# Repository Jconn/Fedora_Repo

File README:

README file for the MAAV EAGLE git repo

*Do not add gerber files or zip files to the repo

*Edit the .gitignore file with any extensions that for gerber files if encountered

*Don't forget to add your name and email address your local config

*If you find errors in libraries, please fix them imediately or contact the author to report the error.

*You should not trust any of the files in this repo.  PLEASE VERIFY ALL COMPONENTS FOR YOURSELF!

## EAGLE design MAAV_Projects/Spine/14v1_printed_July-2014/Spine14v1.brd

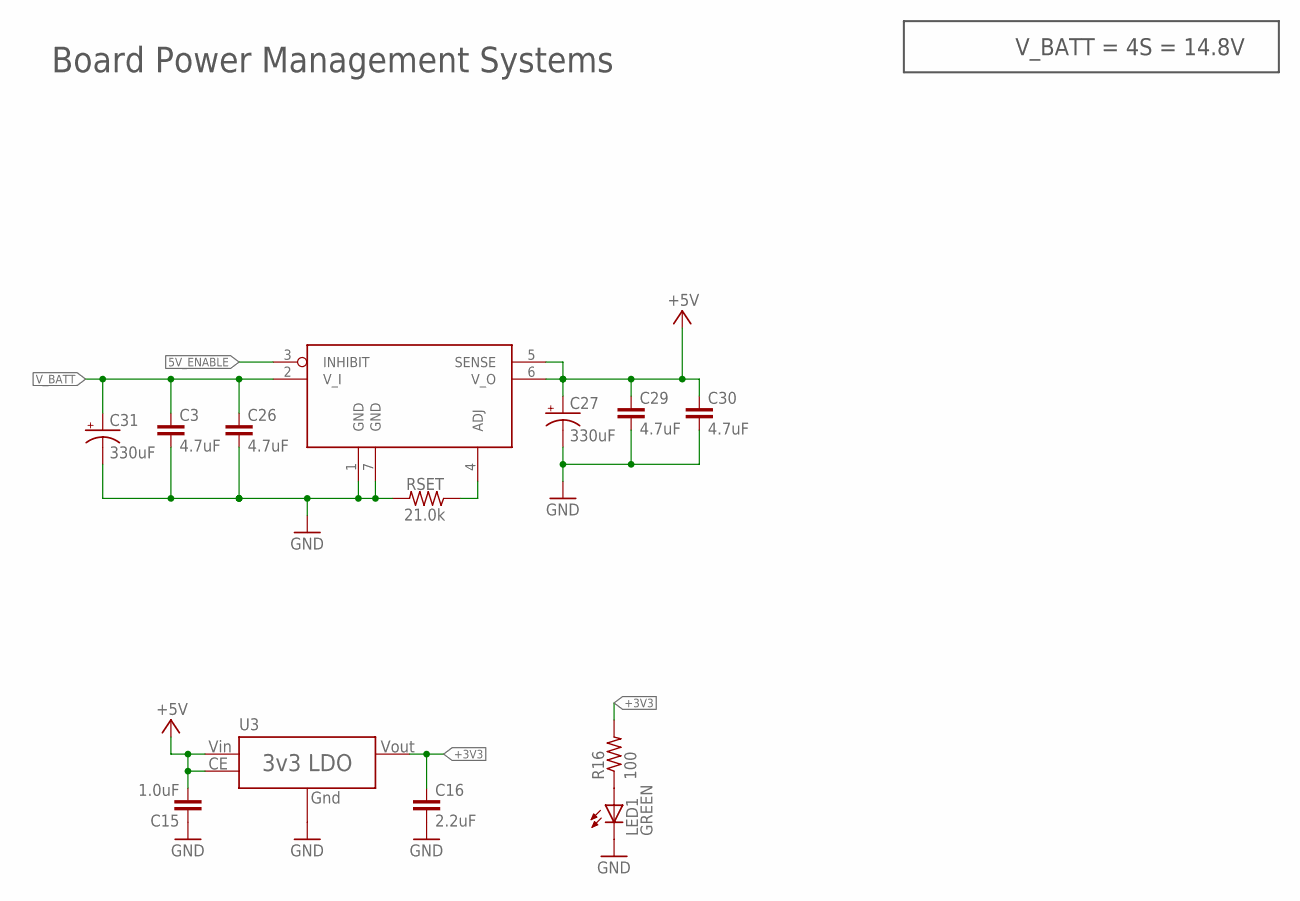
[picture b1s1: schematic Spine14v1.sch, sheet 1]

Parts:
C3, C26, C29, C30: 4.7uF; C1206; DIGIKEY# 587-2994-1-ND
C15: 1.0uF; C0805
C16: 2.2uF; C0805
C27, C31: 330uF; PANASONIC_F; DIGIKEY PCE3779CT-ND
LED1: GREEN; CHIPLED_0603
R16: 100; R0603
RSET: 21.0k; R0603
U3: XC6210; SOT-25
U$5: POWER-MODULE-TI-6A_SOLDERLESS_TERMINAL; POWER-MOD-TI-6A-SOLDERLESS-TERMINAL

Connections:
5V_ENABLE: U$5.3 (INHIBIT); also elsewhere on the board
+3V3: C16.1, R16.2, U3.5 (VOUT); also elsewhere on the board
+5V: C15.2, C27.+, C29.1, C30.1, U3.1 (VIN), U3.3 (CE), U$5.5 (SENSE), U$5.6 (V_O); also elsewhere on the board
GND: C3.2, C15.1, C16.2, C26.2, C27.-, C29.2, C30.2, C31.-, LED1.C, RSET.2, U3.2 (GND), U$5.1 (GND), U$5.7 (GND); also elsewhere on the board
unnamed: LED1.A, R16.1
unnamed: RSET.1, U$5.4 (ADJ)
V_BATT: C3.1, C26.1, C31.+, U$5.2 (V_I); also elsewhere on the board

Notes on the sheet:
Board Power Management Systems
V_BATT = 4S = 14.8V

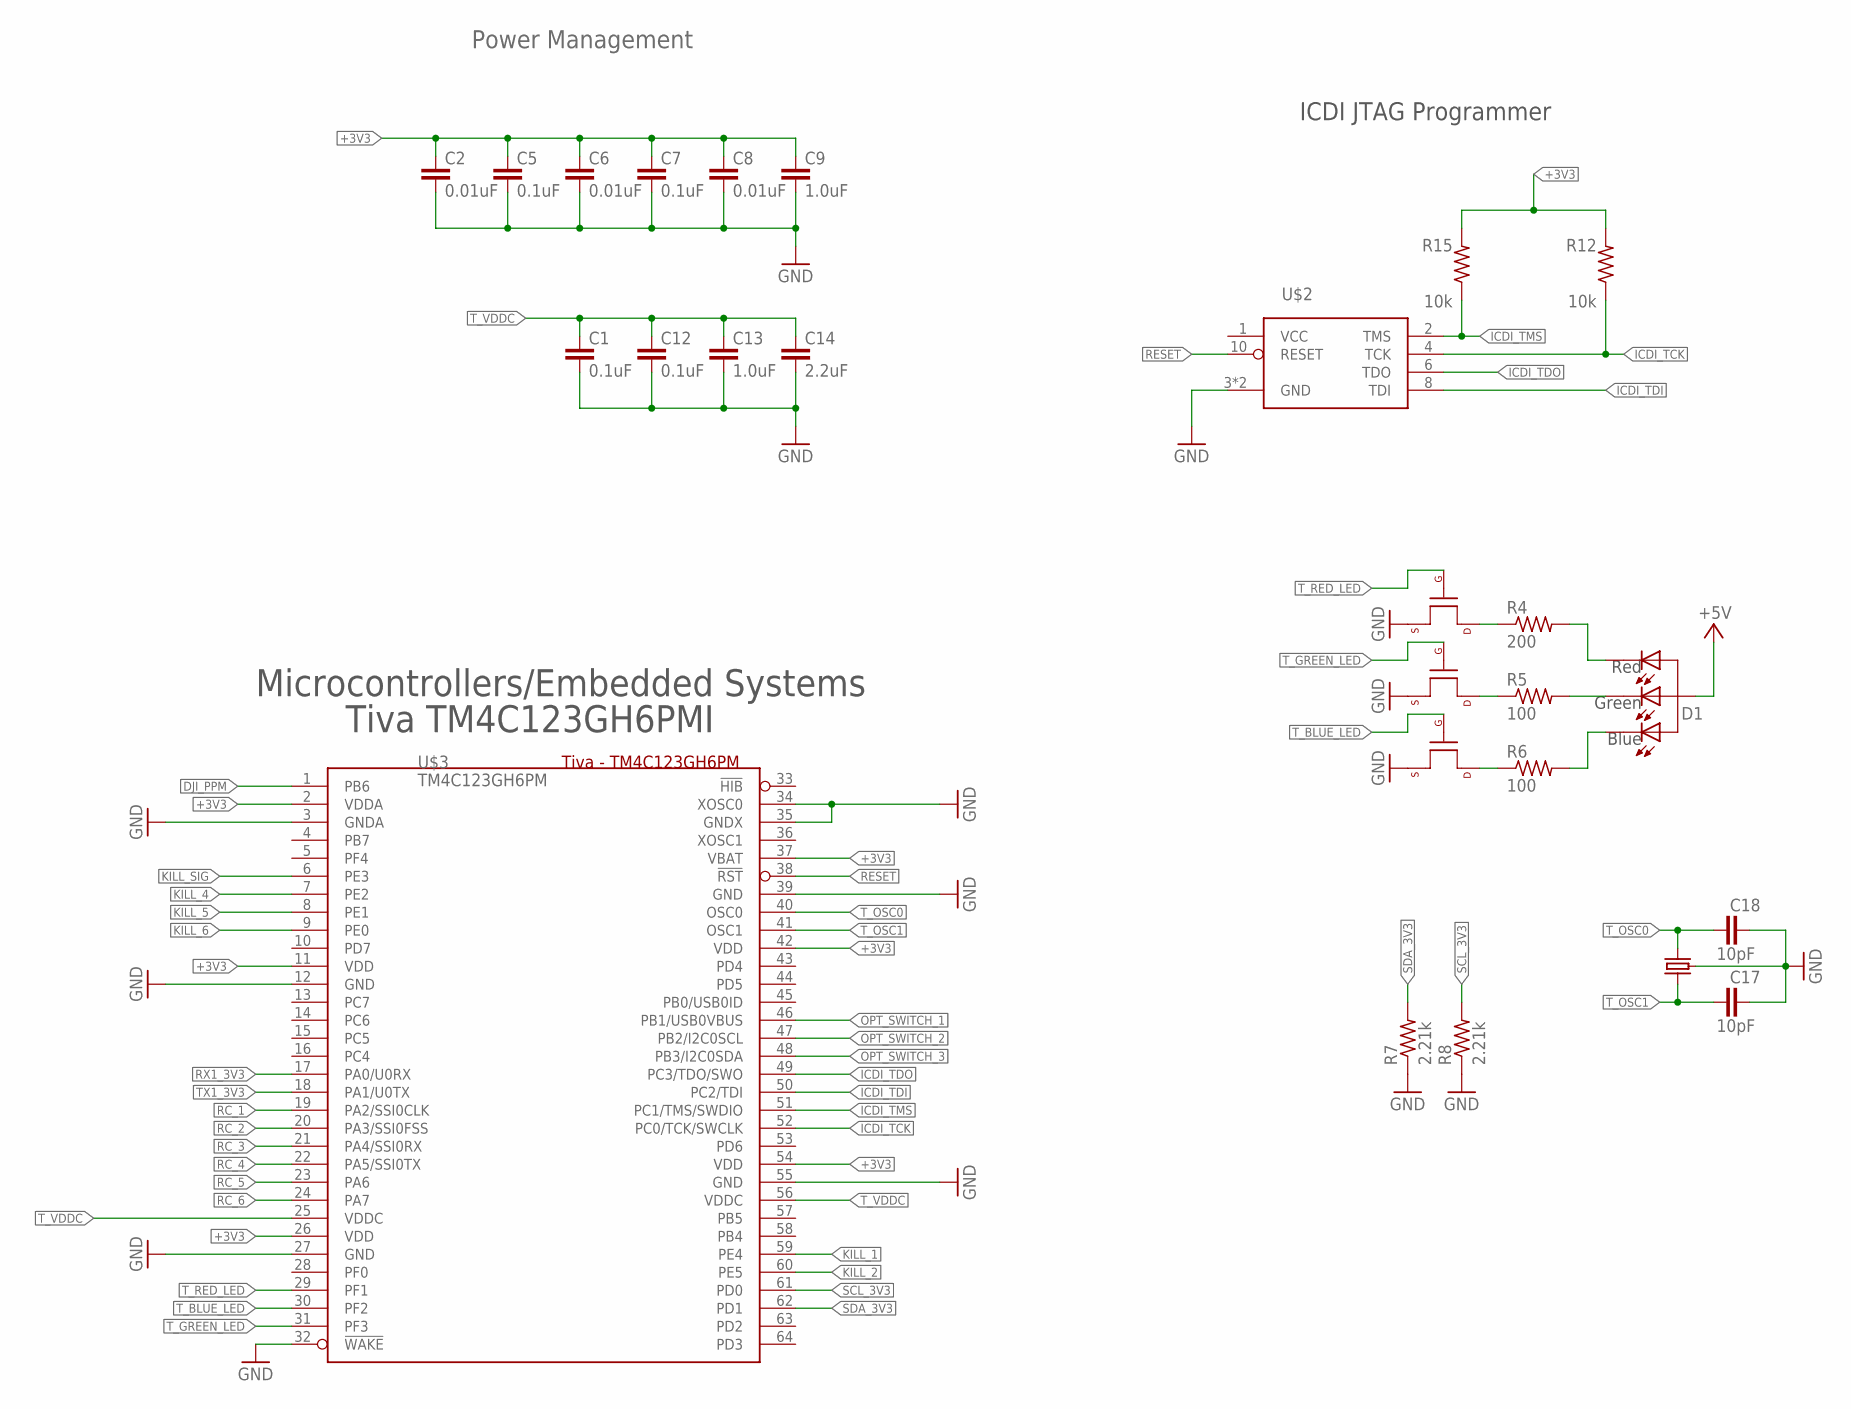
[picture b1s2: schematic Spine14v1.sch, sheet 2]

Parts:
C1, C5, C7, C12: 0.1uF; C0603
C2, C6, C8: 0.01uF; C0603
C9: 1.0uF; C0603
C13: 1.0uF; C0805
C14: 2.2uF; C0805
C17, C18: 10pF; C0603; DIGIKEY# 399-1049-1-ND
D1: LED_RGB_CA; LED_RGB_0606
Q2, Q3, Q4: MOSFET-NCHANNELSMD; SOT23-3; DIGIKEY# BSN20-7DICT-ND
R4: 200; R0603
R5, R6: 100; R0603
R7, R8: 2.21k; R0603
R12, R15: 10k; R0603
U$1: CRYSTAL_403C11E16; 4-SMD-SWITCH
U$2: JTAG-ARM_TC-10; TC2050-IDC
U$3: TM4C123GH6PM; DIGIKEY# 296-35849-ND

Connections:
+3V3: C2.1, C5.1, C6.1, C7.1, C8.1, C9.1, R12.2, R15.2, U$3.2 (VDDA), U$3.11 (VDD), U$3.26 (VDD), U$3.37 (VBAT), U$3.42 (VDD), U$3.54 (VDD); also elsewhere on the board
+5V: D1.1 (A); also elsewhere on the board
DJI_PPM: U$3.1 (PB6); also elsewhere on the board
GND: C1.2, C2.2, C5.2, C6.2, C7.2, C8.2, C9.2, C12.2, C13.2, C14.2, C17.2, C18.2, Q2.2 (S), Q3.2 (S), Q4.2 (S), R7.1, R8.1, U$1.2 (GND), U$1.4 (GND), U$2.3 (GND), U$2.9 (GND), U$3.3 (GNDA), U$3.12 (GND), U$3.27 (GND), U$3.32 (!WAKE), U$3.34 (XOSC0), U$3.35 (GNDX), U$3.39 (GND), U$3.55 (GND); also elsewhere on the board
ICDI_TCK: R12.1, U$2.4 (TCK), U$3.52 (PC0/TCK/SWCLK)
ICDI_TDI: U$2.8 (TDI), U$3.50 (PC2/TDI)
ICDI_TDO: U$2.6 (TDO), U$3.49 (PC3/TDO/SWO)
ICDI_TMS: R15.1, U$2.2 (TMS), U$3.51 (PC1/TMS/SWDIO)
KILL_1: U$3.59 (PE4); also elsewhere on the board
KILL_2: U$3.60 (PE5); also elsewhere on the board
KILL_4: U$3.7 (PE2); also elsewhere on the board
KILL_5: U$3.8 (PE1); also elsewhere on the board
KILL_6: U$3.9 (PE0); also elsewhere on the board
KILL_SIG: U$3.6 (PE3); also elsewhere on the board
unnamed: Q4.3 (D), R4.1
unnamed: Q3.3 (D), R5.1
unnamed: Q2.3 (D), R6.1
unnamed: D1.2 (R), R4.2
unnamed: D1.3 (G), R5.2
unnamed: D1.4 (B), R6.2
OPT_SWITCH_1: U$3.46 (PB1/USB0VBUS); also elsewhere on the board
OPT_SWITCH_2: U$3.47 (PB2/I2C0SCL); also elsewhere on the board
OPT_SWITCH_3: U$3.48 (PB3/I2C0SDA); also elsewhere on the board
RC_1: U$3.19 (PA2/SSI0CLK); also elsewhere on the board
RC_2: U$3.20 (PA3/SSI0FSS); also elsewhere on the board
RC_3: U$3.21 (PA4/SSI0RX); also elsewhere on the board
RC_4: U$3.22 (PA5/SSI0TX); also elsewhere on the board
RC_5: U$3.23 (PA6); also elsewhere on the board
RC_6: U$3.24 (PA7); also elsewhere on the board
RESET: U$2.10 (RESET), U$3.38 (!RST); also elsewhere on the board
RX1_3V3: U$3.17 (PA0/U0RX); also elsewhere on the board
SCL_3V3: R8.2, U$3.61 (PD0); also elsewhere on the board
SDA_3V3: R7.2, U$3.62 (PD1); also elsewhere on the board
TX1_3V3: U$3.18 (PA1/U0TX); also elsewhere on the board
T_BLUE_LED: Q2.1 (G), U$3.30 (PF2)
T_GREEN_LED: Q3.1 (G), U$3.31 (PF3)
T_OSC0: C18.1, U$1.3 (2), U$3.40 (OSC0)
T_OSC1: C17.1, U$1.1, U$3.41 (OSC1)
T_RED_LED: Q4.1 (G), U$3.29 (PF1)
T_VDDC: C1.1, C12.1, C13.1, C14.1, U$3.25 (VDDC), U$3.56 (VDDC)

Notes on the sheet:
Microcontrollers/Embedded Systems
Power Management
Tiva TM4C123GH6PMI
ICDI JTAG Programmer

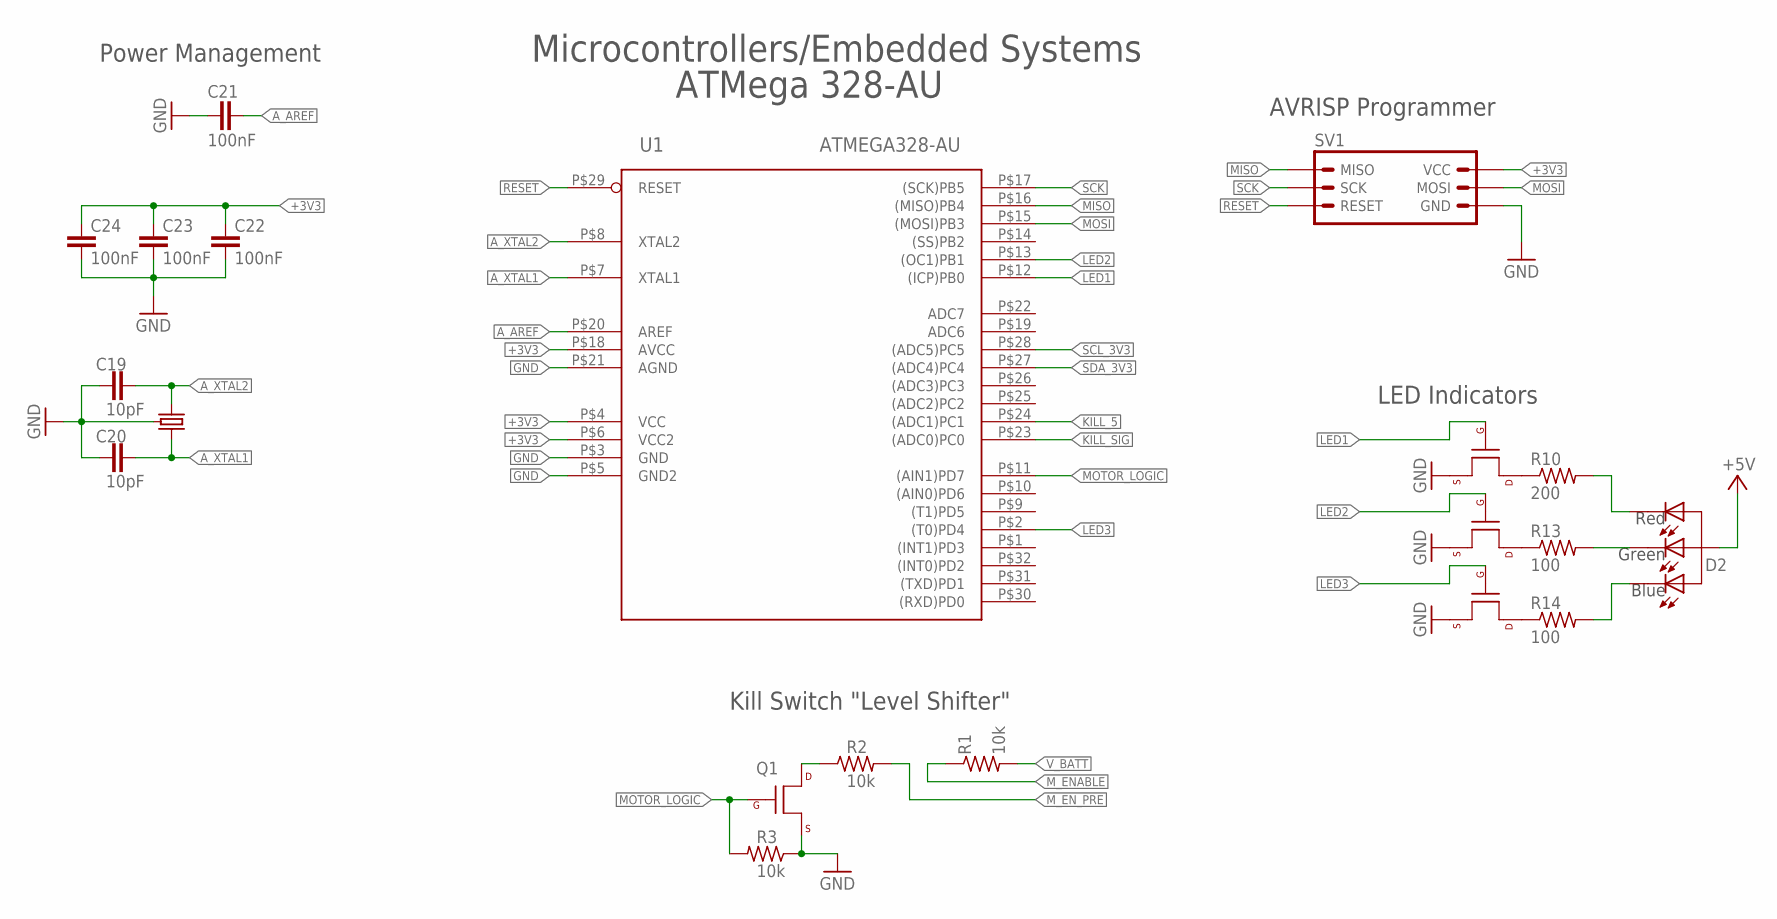
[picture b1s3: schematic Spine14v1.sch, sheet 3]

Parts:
C19, C20: 10pF; C0603; DIGIKEY# 399-1049-1-ND
C21, C22, C23, C24: 100nF; C0603; DIGIKEY# 1276-1000-1-ND
D2: LED_RGB_CA; LED_RGB_0606
Q1, Q6, Q7, Q8: MOSFET-NCHANNELSMD; SOT23-3; DIGIKEY# BSN20-7DICT-ND
R1, R2, R3: 10k; R0603
R10: 200; R0603
R13, R14: 100; R0603
SV1: AVRISP-6_3X2_PLUG_OF_NAILS; TC2030-IDC
U1: ATMEGA328-AU; 32-TQFP; DIGIKEY# ATMEGA328-AU-ND
U$6: CRYSTAL_403C11E16; 4-SMD-SWITCH

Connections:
+3V3: C22.1, C23.1, C24.1, SV1.6 (VCC), U1.P$4 (VCC), U1.P$6 (VCC2), U1.P$18 (AVCC); also elsewhere on the board
+5V: D2.1 (A); also elsewhere on the board
A_AREF: C21.1, U1.P$20 (AREF)
A_XTAL1: C20.2, U1.P$7 (XTAL1), U$6.3 (2)
A_XTAL2: C19.2, U1.P$8 (XTAL2), U$6.1
GND: C19.1, C20.1, C21.2, C22.2, C23.2, C24.2, Q1.2 (S), Q6.2 (S), Q7.2 (S), Q8.2 (S), R3.1, SV1.4 (GND), U1.P$3 (GND), U1.P$5 (GND2), U1.P$21 (AGND), U$6.2 (GND), U$6.4 (GND); also elsewhere on the board
KILL_5: U1.P$24 ((ADC1)PC1); also elsewhere on the board
KILL_SIG: U1.P$23 ((ADC0)PC0); also elsewhere on the board
LED1: Q8.1 (G), U1.P$12 ((ICP)PB0)
LED2: Q7.1 (G), U1.P$13 ((OC1)PB1)
LED3: Q6.1 (G), U1.P$2 ((T0)PD4)
MISO: SV1.1 (MISO), U1.P$16 ((MISO)PB4)
MOSI: SV1.5 (MOSI), U1.P$15 ((MOSI)PB3)
MOTOR_LOGIC: Q1.1 (G), R3.2, U1.P$11 ((AIN1)PD7)
M_ENABLE: R1.1; also elsewhere on the board
M_EN_PRE: R2.2; also elsewhere on the board
unnamed: Q1.3 (D), R2.1
unnamed: Q8.3 (D), R10.1
unnamed: Q7.3 (D), R13.1
unnamed: Q6.3 (D), R14.1
unnamed: D2.2 (R), R10.2
unnamed: D2.3 (G), R13.2
unnamed: D2.4 (B), R14.2
RESET: SV1.3 (RESET), U1.P$29 (RESET); also elsewhere on the board
SCK: SV1.2 (SCK), U1.P$17 ((SCK)PB5)
SCL_3V3: U1.P$28 ((ADC5)PC5); also elsewhere on the board
SDA_3V3: U1.P$27 ((ADC4)PC4); also elsewhere on the board
V_BATT: R1.2; also elsewhere on the board

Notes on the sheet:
Microcontrollers/Embedded Systems
ATMega 328-AU
AVRISP Programmer
Power Management
LED Indicators
Kill Switch "Level Shifter"

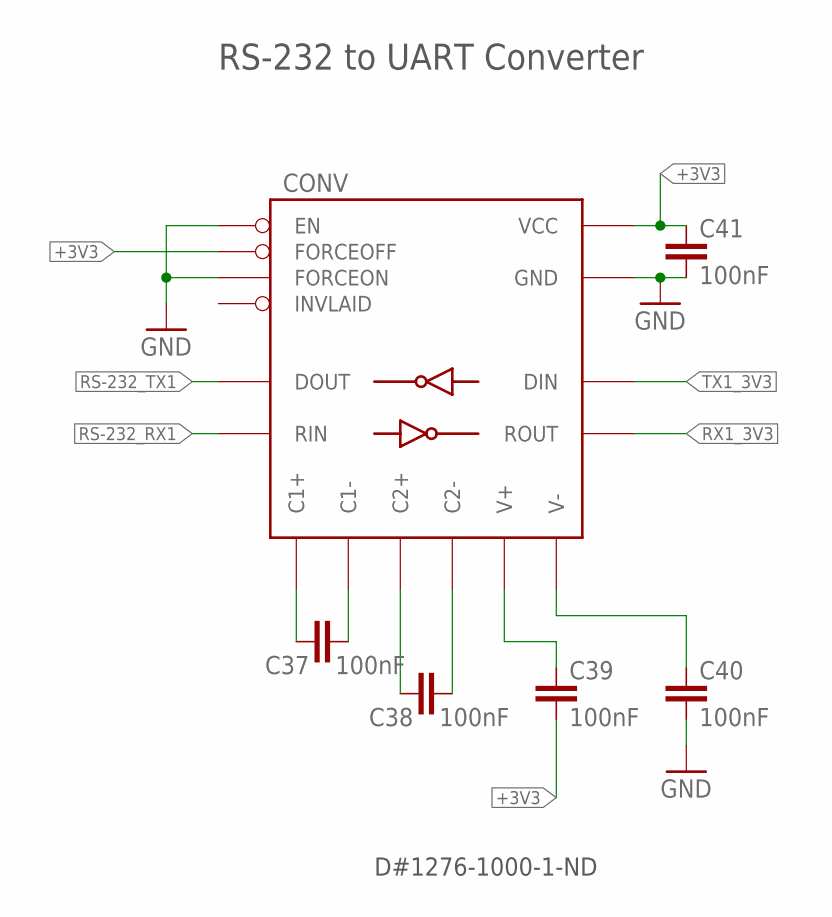
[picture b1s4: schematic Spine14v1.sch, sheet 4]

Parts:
C37, C41: 100nF; C0603; DIGIKEY# 1276-1000-1-ND
C38, C39, C40: 100nF; C0805
CONV: MAX3221-RS232; 16-TSSOP; DIGIKEY# 296-19825-1-ND

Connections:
+3V3: C39.2, C41.1, CONV.P$15 (VCC), CONV.P$16 (FORCEOFF); also elsewhere on the board
GND: C40.2, C41.2, CONV.P$1 (EN), CONV.P$12 (FORCEON), CONV.P$14 (GND); also elsewhere on the board
unnamed: C37.1, CONV.P$2 (C1+)
unnamed: C39.1, CONV.P$3 (V+)
unnamed: C40.1, CONV.P$7 (V-)
unnamed: C37.2, CONV.P$4 (C1-)
unnamed: C38.1, CONV.P$5 (C2+)
unnamed: C38.2, CONV.P$6 (C2-)
RS-232_RX1: CONV.P$8 (RIN); also elsewhere on the board
RS-232_TX1: CONV.P$13 (DOUT); also elsewhere on the board
RX1_3V3: CONV.P$9 (ROUT); also elsewhere on the board
TX1_3V3: CONV.P$11 (DIN); also elsewhere on the board

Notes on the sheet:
RS-232 to UART Converter
D#1276-1000-1-ND

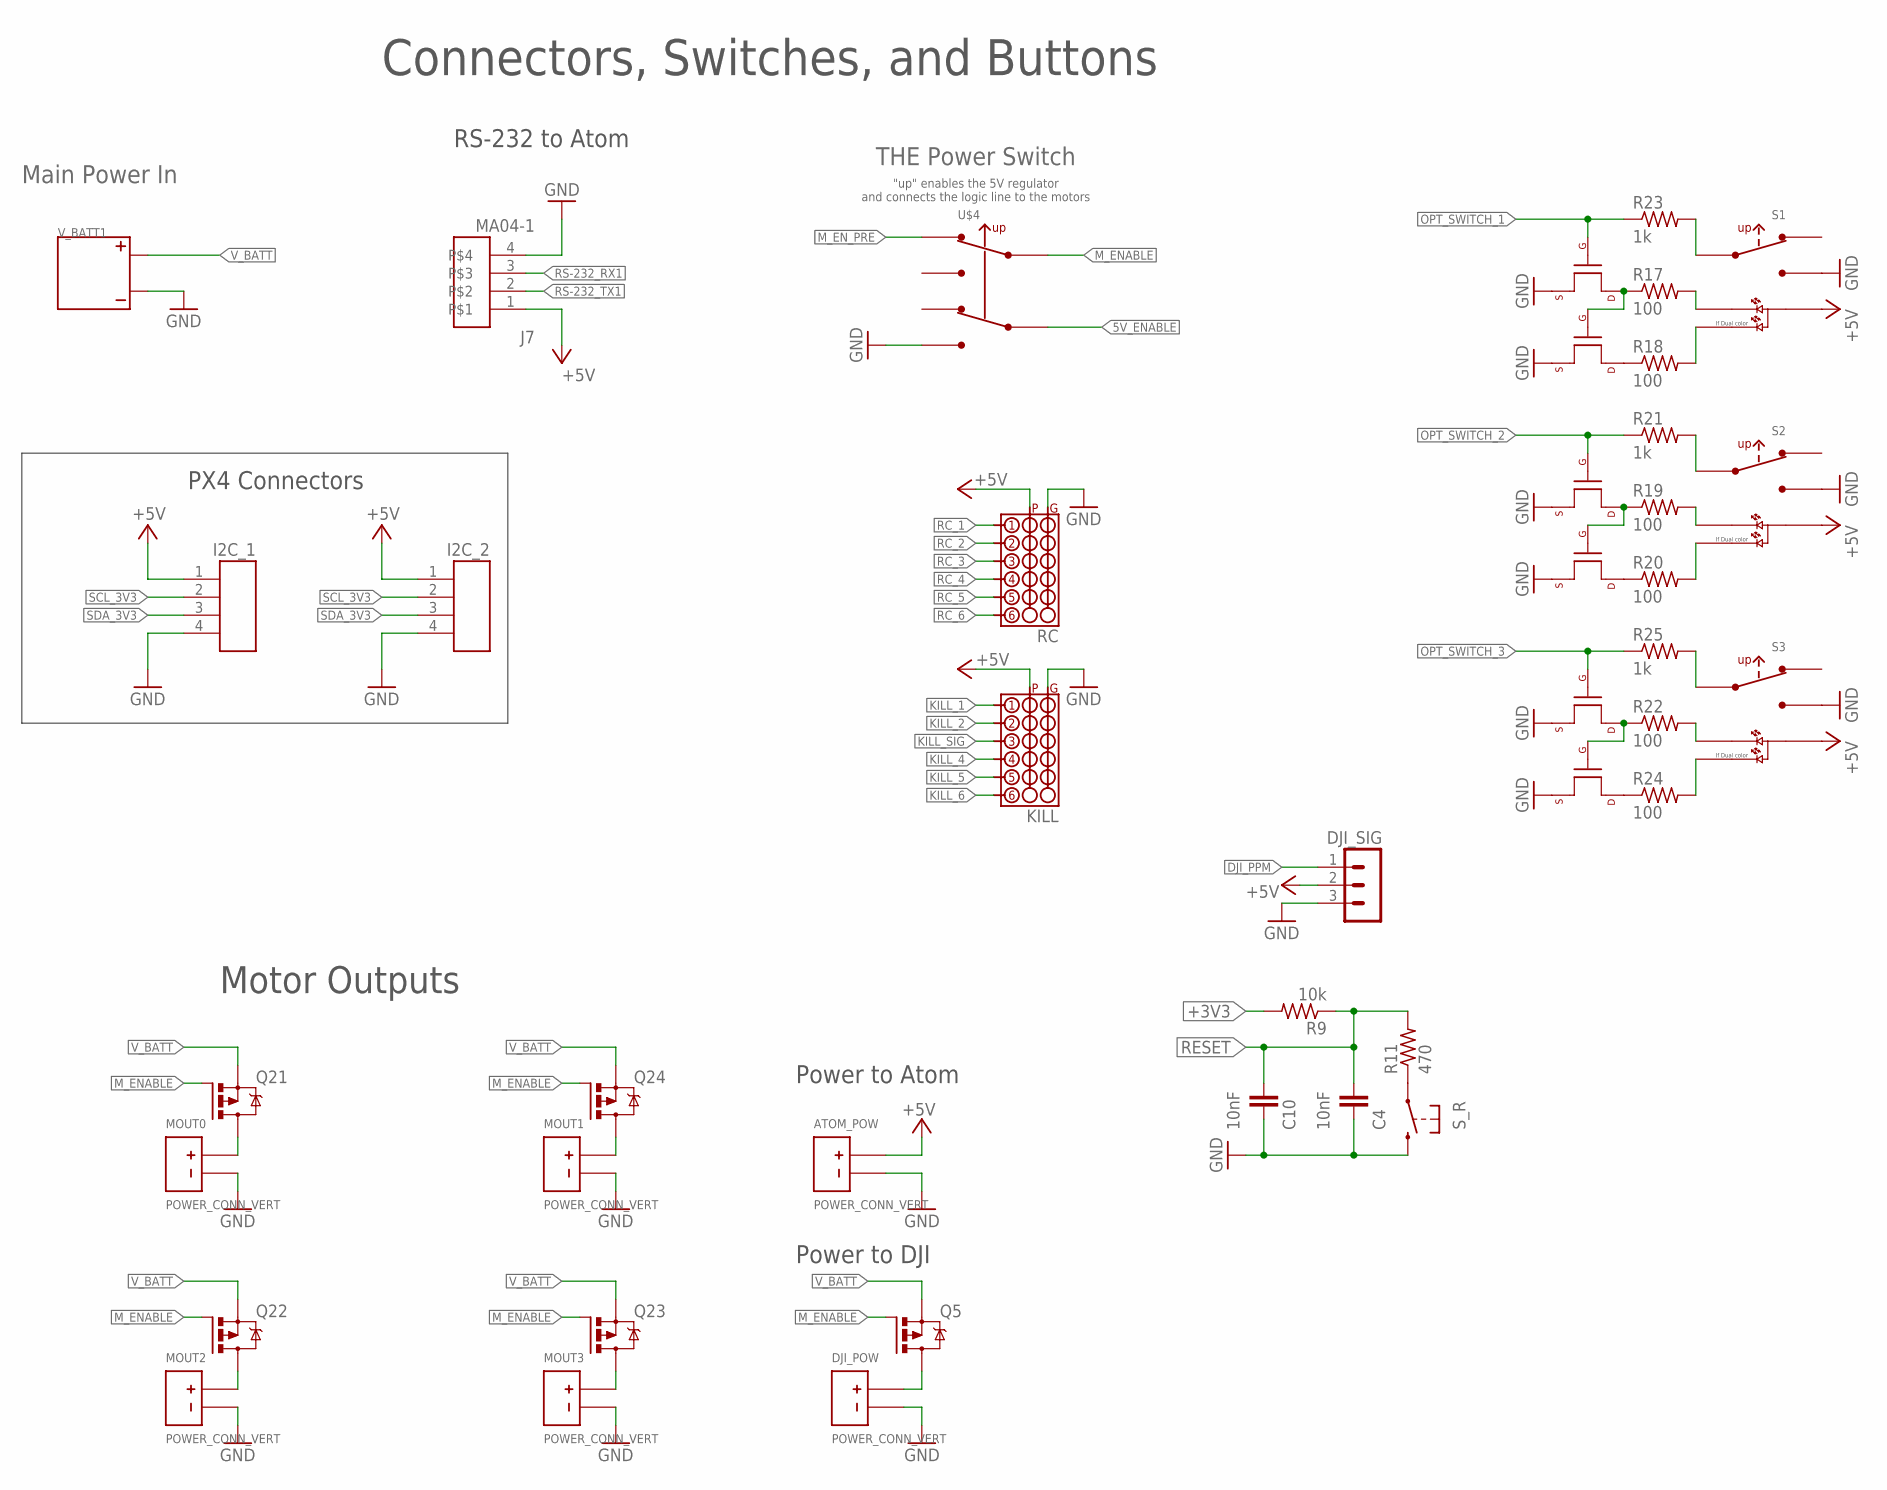
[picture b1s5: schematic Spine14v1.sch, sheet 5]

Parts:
ATOM_POW: POWER_CONN_VERT; POWER_CONN
C4, C10: 10nF; C0603
DJI_POW: POWER_CONN_VERT; POWER_CONN
DJI_SIG: MA03-1
I2C_1, I2C_2: CONN_HEADER_4POS_RIGHT_ANGLE_I2C; CONN_HEADER_4POS_1.25MM_SMD
J7: MA04-1; MA-04-SMD
KILL: RC_RECIEVER_RECEP
MOUT0, MOUT1, MOUT2, MOUT3: POWER_CONN_VERT; POWER_CONN
Q5, Q21, Q22, Q23, Q24: P-MOSFET-SO8POWER-PAK; SO-8_POWER-PAK
Q9, Q10, Q11, Q12, Q13, Q14: MOSFET-NCHANNELSMD; SOT23-3; DIGIKEY# BSN20-7DICT-ND
R9: 10k; R0603
R11: 470; R0603
R17, R18, R19, R20, R22, R24: 100; R0603
R21, R23, R25: 1k; R0603
RC: RC_RECIEVER_RECEP
S1, S2, S3: SWITCH_SPDT_ILUMINATED_2COLOR_VERT_ILLUMINATED; NKK_VERT_SWITCH_6PIN
S_R: TACT_BUTTONSMD; TACT-MOM-SMD
U$4: JON_LIB_SWITCH_DPDT; JON_LIB_SWITCH_VERT_DPDT
V_BATT1: BATT-CONN-50A_MINI-FIT-SR_THRU-HOLE; BATT-CONN-50A

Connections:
5V_ENABLE: U$4.P$5; also elsewhere on the board
+3V3: R9.2; also elsewhere on the board
+5V: ATOM_POW.P1, DJI_SIG.2, I2C_1.1, I2C_2.1, J7.1, KILL.VCC, KILL.VCC2 (VCC), RC.VCC, RC.VCC2 (VCC), S1.P$5, S2.P$5, S3.P$5; also elsewhere on the board
DJI_PPM: DJI_SIG.1; also elsewhere on the board
GND: ATOM_POW.P2 (N), C4.2, C10.2, DJI_POW.P2 (N), DJI_SIG.3, I2C_1.4, I2C_2.4, J7.4, KILL.GND, KILL.GND2 (GND), MOUT0.P2 (N), MOUT1.P2 (N), MOUT2.P2 (N), MOUT3.P2 (N), Q9.2 (S), Q10.2 (S), Q11.2 (S), Q12.2 (S), Q13.2 (S), Q14.2 (S), RC.GND, RC.GND2 (GND), S1.P$1, S2.P$1, S3.P$1, S_R.S, S_R.S1 (S), U$4.P$6, V_BATT1.GND-1 (GND), V_BATT1.GND-2 (GND); also elsewhere on the board
KILL_1: KILL.P$1; also elsewhere on the board
KILL_2: KILL.P$2; also elsewhere on the board
KILL_4: KILL.P$4; also elsewhere on the board
KILL_5: KILL.P$5; also elsewhere on the board
KILL_6: KILL.P$6; also elsewhere on the board
KILL_SIG: KILL.P$3; also elsewhere on the board
M_ENABLE: Q5.G, Q21.G, Q22.G, Q23.G, Q24.G, U$4.P$2; also elsewhere on the board
M_EN_PRE: U$4.P$1; also elsewhere on the board
unnamed: MOUT0.P1, Q21.D1, Q21.D2 (D1), Q21.D3 (D1), Q21.D4 (D1), Q21.D5 (D1)
unnamed: Q9.1 (G), Q10.3 (D), R17.1
unnamed: R11.1, S_R.P, S_R.P1
unnamed: MOUT1.P1, Q24.D1, Q24.D2 (D1), Q24.D3 (D1), Q24.D4 (D1), Q24.D5 (D1)
unnamed: MOUT2.P1, Q22.D1, Q22.D2 (D1), Q22.D3 (D1), Q22.D4 (D1), Q22.D5 (D1)
unnamed: MOUT3.P1, Q23.D1, Q23.D2 (D1), Q23.D3 (D1), Q23.D4 (D1), Q23.D5 (D1)
unnamed: DJI_POW.P1, Q5.D1, Q5.D2 (D1), Q5.D3 (D1), Q5.D4 (D1), Q5.D5 (D1)
unnamed: Q9.3 (D), R18.1
unnamed: Q11.1 (G), Q12.3 (D), R19.1
unnamed: Q11.3 (D), R20.1
unnamed: R19.2, S2.P$6
unnamed: R20.2, S2.P$4
unnamed: R23.2, S1.P$2
unnamed: R21.2, S2.P$2
unnamed: R17.2, S1.P$6
unnamed: R18.2, S1.P$4
unnamed: Q13.1 (G), Q14.3 (D), R22.1
unnamed: Q13.3 (D), R24.1
unnamed: R22.2, S3.P$6
unnamed: R24.2, S3.P$4
unnamed: R25.2, S3.P$2
OPT_SWITCH_1: Q10.1 (G), R23.1; also elsewhere on the board
OPT_SWITCH_2: Q12.1 (G), R21.1; also elsewhere on the board
OPT_SWITCH_3: Q14.1 (G), R25.1; also elsewhere on the board
RC_1: RC.P$1; also elsewhere on the board
RC_2: RC.P$2; also elsewhere on the board
RC_3: RC.P$3; also elsewhere on the board
RC_4: RC.P$4; also elsewhere on the board
RC_5: RC.P$5; also elsewhere on the board
RC_6: RC.P$6; also elsewhere on the board
RESET: C4.1, C10.1, R9.1, R11.2; also elsewhere on the board
RS-232_RX1: J7.3; also elsewhere on the board
RS-232_TX1: J7.2; also elsewhere on the board
SCL_3V3: I2C_1.2, I2C_2.2; also elsewhere on the board
SDA_3V3: I2C_1.3, I2C_2.3; also elsewhere on the board
V_BATT: Q5.S1, Q5.S2 (S1), Q5.S3 (S1), Q21.S1, Q21.S2 (S1), Q21.S3 (S1), Q22.S1, Q22.S2 (S1), Q22.S3 (S1), Q23.S1, Q23.S2 (S1), Q23.S3 (S1), Q24.S1, Q24.S2 (S1), Q24.S3 (S1), V_BATT1.VCC-1 (VCC), V_BATT1.VCC-2 (VCC); also elsewhere on the board

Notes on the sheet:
Connectors, Switches, and Buttons
"up" enables the 5V regulator and connects the logic line to the motors
Main Power In
THE Power Switch
Motor Outputs
PX4 Connectors
RS-232 to Atom
Power to Atom
Power to DJI

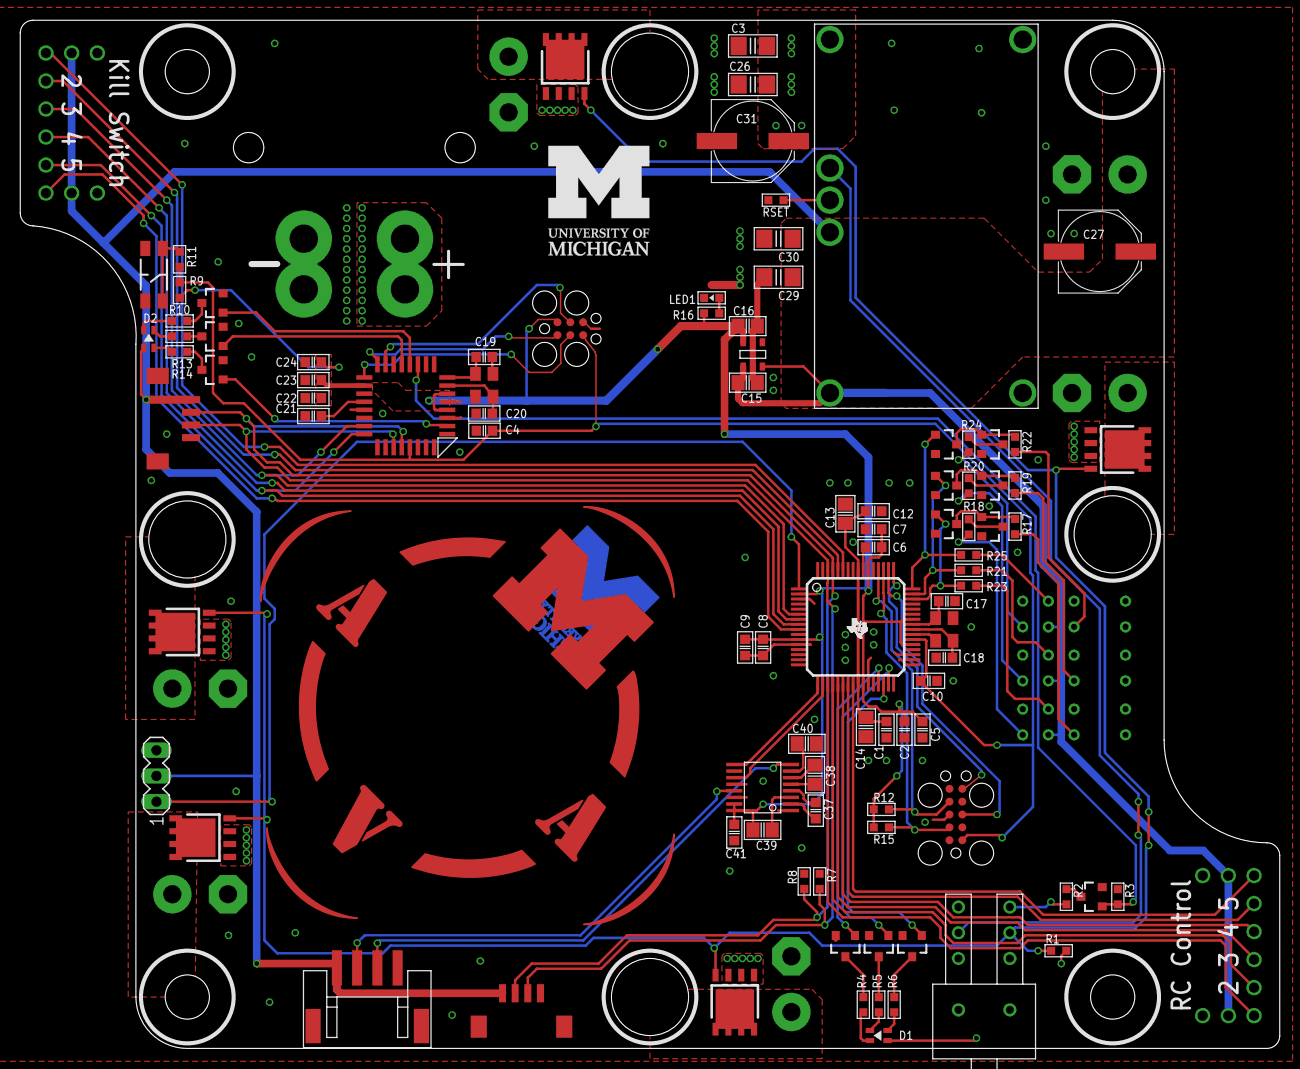
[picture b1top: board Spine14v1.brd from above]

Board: 4 copper layers, 124.5 x 101.6 mm, 110 parts (1 on the bottom side), 92 nets.

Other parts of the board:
U$7: BLOCK-M-DOUBLE-STACKED-10MM-MASK
U$8: MAAVLOGO_50MM_MASK_ONLY
U$9: BLOCK-M-DOUBLE-STACKED-10MM

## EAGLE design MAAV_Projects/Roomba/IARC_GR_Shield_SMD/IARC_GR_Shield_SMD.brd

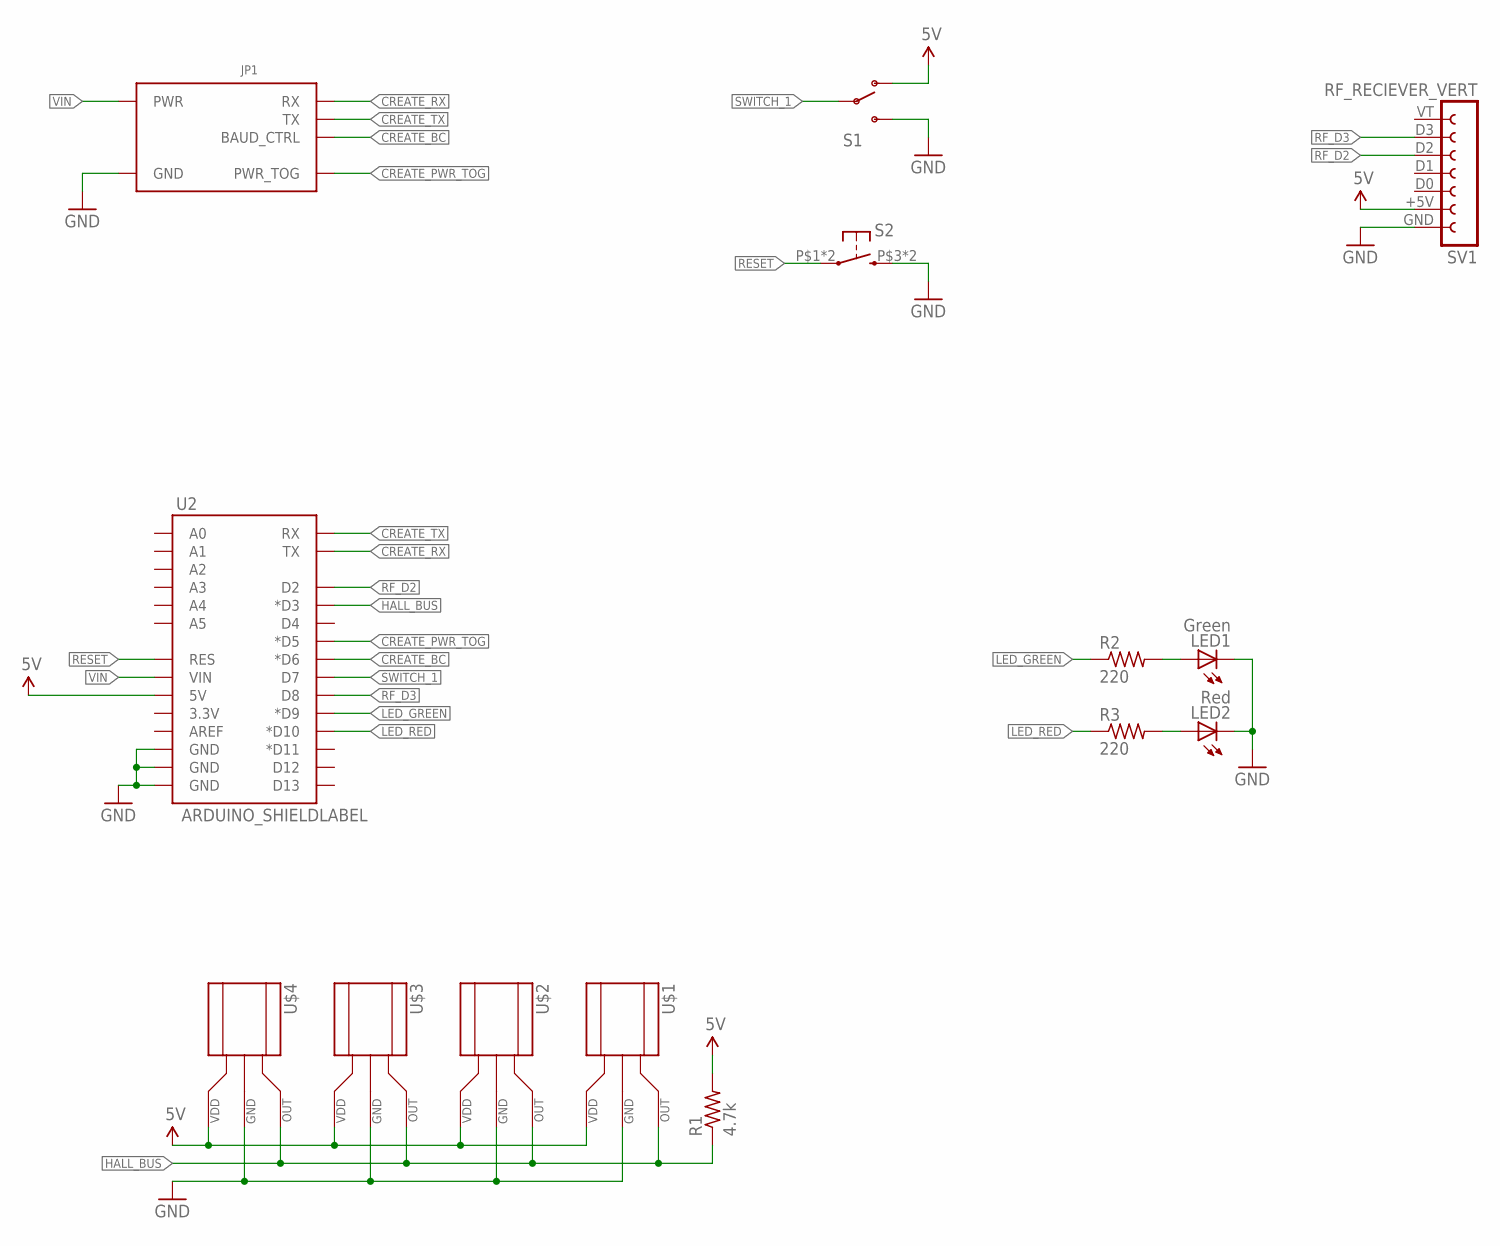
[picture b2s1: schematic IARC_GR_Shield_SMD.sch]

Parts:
JP1: IROBOT_CREATE_IARC_HOOKUP; 2X5-SHROUDED
LED1: Green; CHIPLED_0603
LED2: Red; CHIPLED_0603
R1: 4.7k; R0603
R2, R3: 220; R0603; DIGIKEY# P220HCT-ND
S1: SWITCH-SPDTTHRU-VERT; SWITCH-SPDT_THRU-VERT
S2: TACT_BUTTON_SMD; SIMPLE_BUTTON_SMD
SV1: RF_RECIEVER_VERT
U2: ARDUINO_SHIELDLABEL; DUEMILANOVE_SHIELD
U$1, U$2, U$3, U$4: HALL_EFFECTHEADER; 1X03

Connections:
5V: R1.2, S1.1 (O), SV1.+5V, U2.5V, U$1.1 (VDD), U$2.1 (VDD), U$3.1 (VDD), U$4.1 (VDD)
CREATE_BC: JP1.3 (BAUD_CTRL), U2.D6 (*D6)
CREATE_PWR_TOG: JP1.5 (PWR_TOG), U2.D5 (*D5)
CREATE_RX: JP1.4 (RX), U2.TX
CREATE_TX: JP1.1 (TX), U2.RX
GND: JP1.2 (GND), LED1.C, LED2.C, S1.3 (S), S2.P$3 (S), S2.P$4 (S), SV1.GND, U2.GND@0 (GND), U2.GND@1 (GND), U2.GND@2 (GND), U$1.2 (GND), U$2.2 (GND), U$3.2 (GND), U$4.2 (GND)
HALL_BUS: R1.1, U2.D3 (*D3), U$1.3 (OUT), U$2.3 (OUT), U$3.3 (OUT), U$4.3 (OUT)
LED_GREEN: R2.1, U2.D9 (*D9)
LED_RED: R3.1, U2.D10 (*D10)
unnamed: LED1.A, R2.2
unnamed: LED2.A, R3.2
RESET: S2.P$1, S2.P$2, U2.RES
RF_D2: SV1.D2, U2.D2
RF_D3: SV1.D3, U2.D8
SWITCH_1: S1.2, U2.D7
VIN: JP1.6 (PWR), U2.VIN

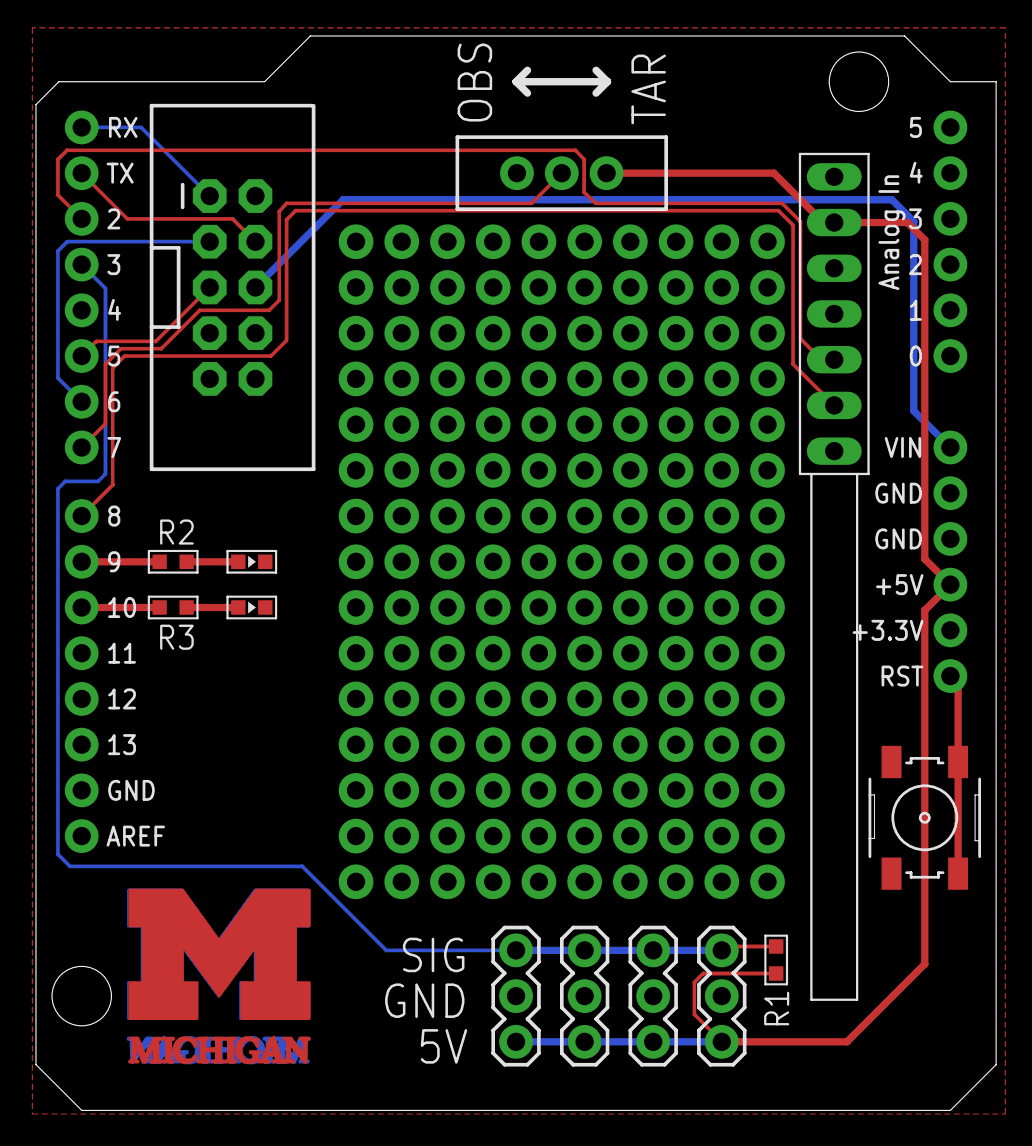
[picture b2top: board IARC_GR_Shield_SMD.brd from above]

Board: 2 copper layers, 53.3 x 59.7 mm, 16 parts (1 on the bottom side), 16 nets.

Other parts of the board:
U$12, U$13: BLOCK-M-STACKED_10MM_MASK

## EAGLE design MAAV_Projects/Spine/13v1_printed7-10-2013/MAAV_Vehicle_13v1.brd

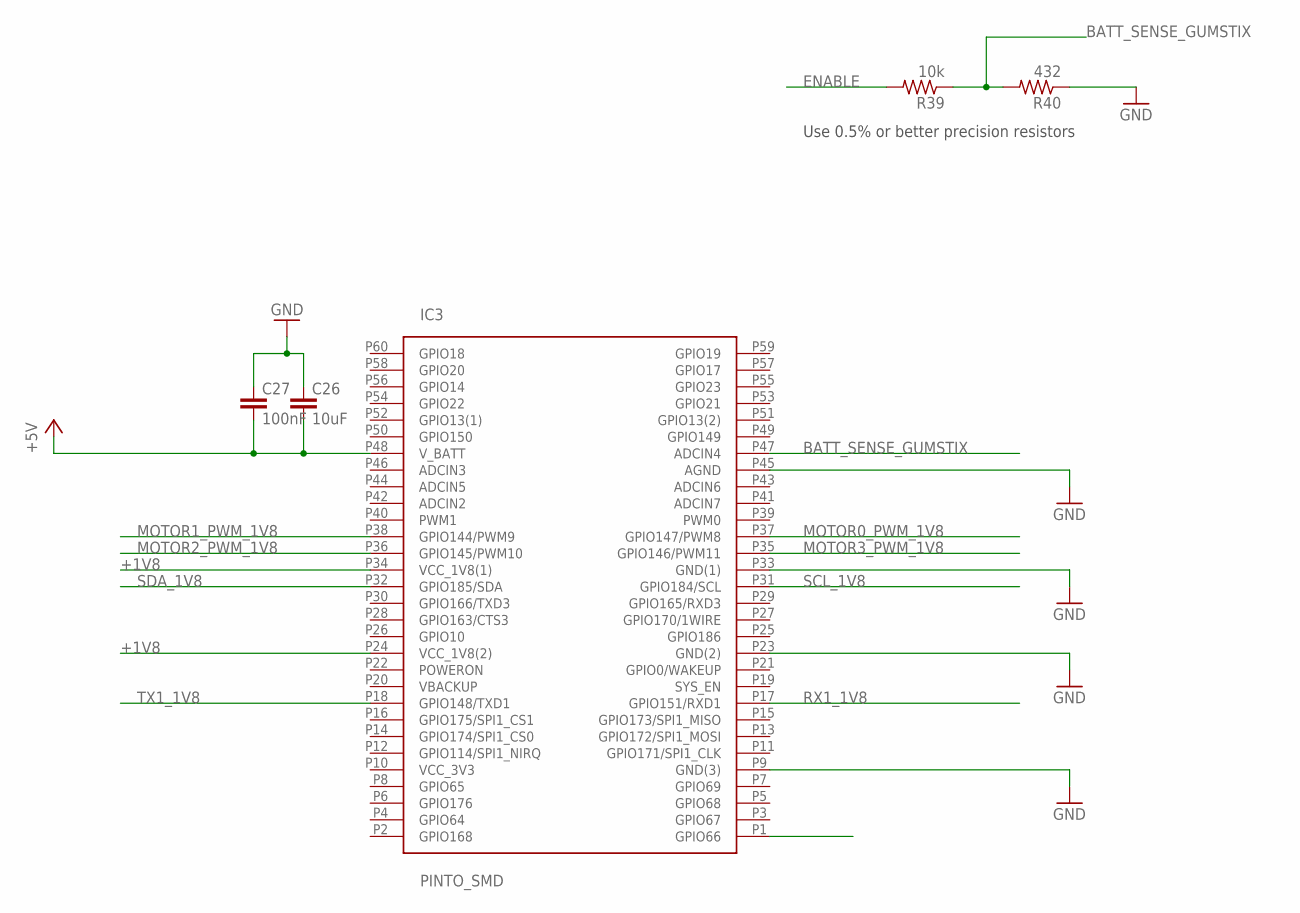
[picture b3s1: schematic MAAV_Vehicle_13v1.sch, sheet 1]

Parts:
C26: 10uF; C1206; DIGIKEY# 587-2399-1-ND
C27: 100nF; C0603; DIGIKEY# 1276-1000-1-ND
IC3: PINTO_SMD; DIGIKEY# S5641-ND (6)
R39: 10k; R0603; DIGIKEY# P10KDBCT-ND
R40: 432; R0603; DIGIKEY# P432DBCT-ND

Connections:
+1V8: IC3.P24 (VCC_1V8(2)), IC3.P34 (VCC_1V8(1)); also elsewhere on the board
+5V: C26.2, C27.2, IC3.P48 (V_BATT); also elsewhere on the board
BATT_SENSE_GUMSTIX: IC3.P47 (ADCIN4), R39.1, R40.2
ENABLE: R39.2; also elsewhere on the board
GND: C26.1, C27.1, IC3.P9 (GND(3)), IC3.P23 (GND(2)), IC3.P33 (GND(1)), IC3.P45 (AGND), R40.1; also elsewhere on the board
MOTOR0_PWM_1V8: IC3.P37 (GPIO147/PWM8); also elsewhere on the board
MOTOR1_PWM_1V8: IC3.P38 (GPIO144/PWM9); also elsewhere on the board
MOTOR2_PWM_1V8: IC3.P36 (GPIO145/PWM10); also elsewhere on the board
MOTOR3_PWM_1V8: IC3.P35 (GPIO146/PWM11); also elsewhere on the board
RX1_1V8: IC3.P17 (GPIO151/RXD1); also elsewhere on the board
SCL_1V8: IC3.P31 (GPIO184/SCL); also elsewhere on the board
SDA_1V8: IC3.P32 (GPIO185/SDA); also elsewhere on the board
TX1_1V8: IC3.P18 (GPIO148/TXD1); also elsewhere on the board

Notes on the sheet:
Use 0.5% or better precision resistors

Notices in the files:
parts and their libraries:
SparkFun-Boards: Licensing: Creative Commons ShareAlike 4.0 International - https://creativecommons.org/licenses/by-sa/4.0
SparkFun-Resistors: Licensing: CC v3.0 Share-Alike You are welcome to use this library for commercial purposes.
